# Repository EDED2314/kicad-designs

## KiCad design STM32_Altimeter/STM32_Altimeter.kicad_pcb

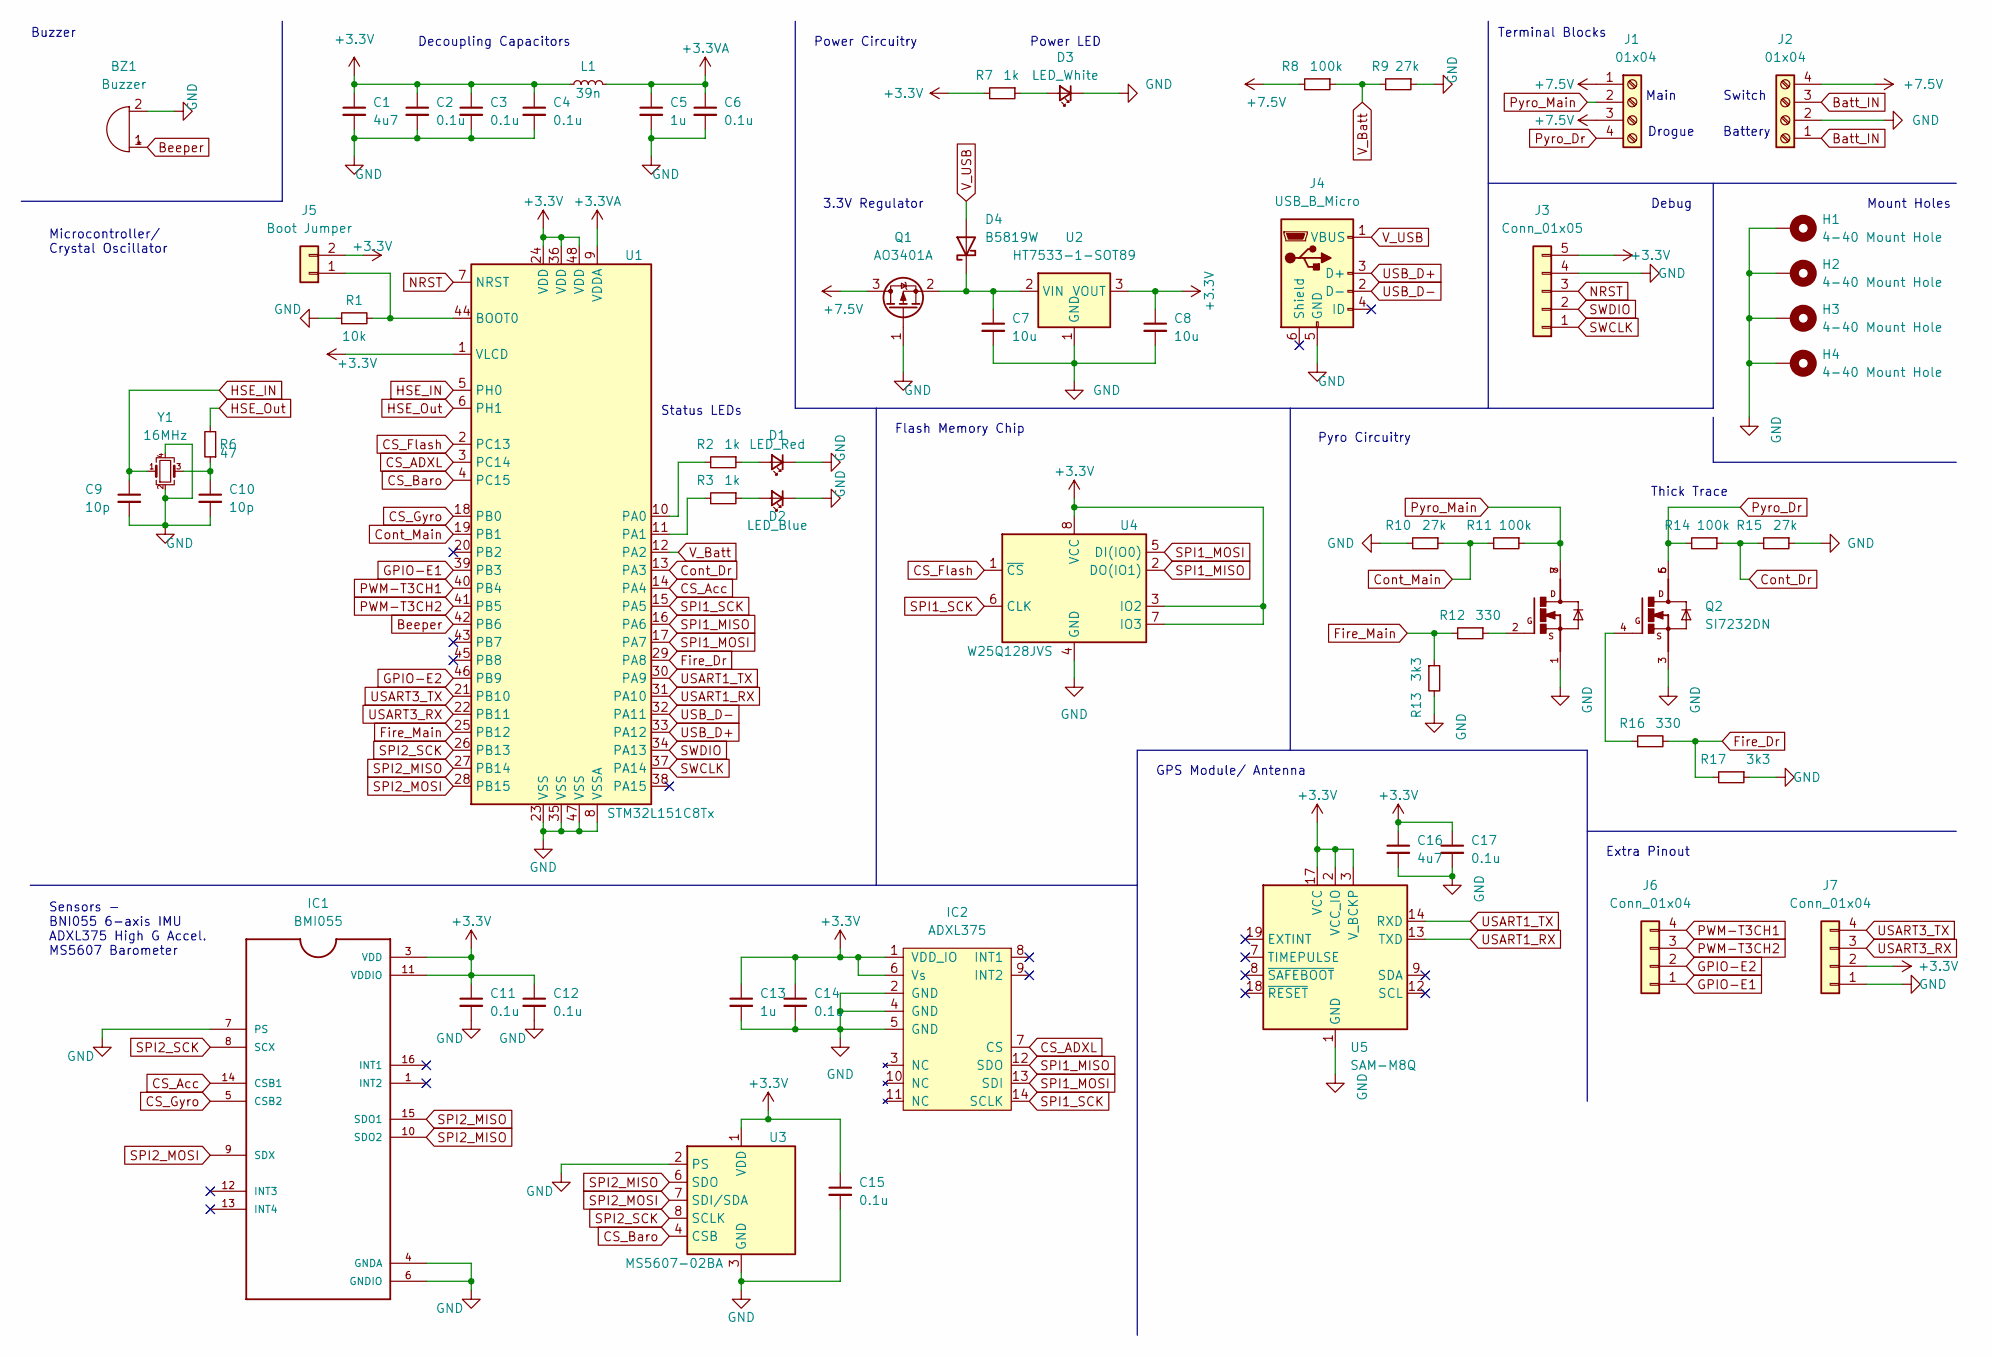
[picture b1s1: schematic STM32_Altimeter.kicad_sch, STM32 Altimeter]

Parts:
BZ1: Buzzer; Buzzer_12x9.5RM7.6
C1, C16: 4u7; C_0402_1005Metric
C2, C3, C4, C6, C11, C12, C14, C15, C17: 0.1u; C_0402_1005Metric
C5, C13: 1u; C_0402_1005Metric
C7, C8: 10u; C_1206_3216Metric
C9, C10: 10p; C_0402_1005Metric
D1: LED_Red; LED_0805_2012Metric
D2: LED_Blue; LED_0805_2012Metric
D3: LED_White; LED_0805_2012Metric
D4: B5819W; D_SOD-123
H1, H2, H3, H4: 4-40 Mount Hole; MountingHole_3.2mm_M3_DIN965_Pad
IC1: BMI055; QFN50P300X450X100-16N
IC2: ADXL375; LCC14P127_600X600X225L91X50N; Farnell 2361527
J1, J2: 01x04; TerminalBlock_MetzConnect_Type011_RT05504HBWC_1x04_P5.00mm_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
J3: Conn_01x05; PinHeader_1x05_P2.54mm_Vertical
J4: USB_B_Micro; USB_Micro-B_Molex-105017-0001
J5: Boot Jumper; PinHeader_1x02_P2.54mm_Vertical
J6: Conn_01x04; JST_SH_BM04B-SRSS-TB_04x1.00mm_Straight
J7: Conn_01x04
L1: 39n; L_0402_1005Metric
Q1: AO3401A; SOT-23
Q2: SI7232DN; TRANS_SI7232DN-T1-GE3
R1: 10k; R_0402_1005Metric
R2, R3, R7: 1k; R_0603_1608Metric
R6: 47; R_0402_1005Metric
R8, R11, R14: 100k; R_0603_1608Metric
R9, R10, R15: 27k; R_0603_1608Metric
R12, R16: 330; R_0402_1005Metric
R13, R17: 3k3; R_0402_1005Metric
U1: STM32L151C8Tx; LQFP-48_7x7mm_P0.5mm
U2: HT7533-1-SOT89; SOT-89-3
U3: MS5607-02BA; LGA-8_3x5mm_P1.25mm
U4: W25Q128JVS; SOIC-8_5.23x5.23mm_P1.27mm
U5: SAM-M8Q; ublox_SAM-M8Q
Y1: 16MHz; Crystal_SMD_3225-4Pin_3.2x2.5mm

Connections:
+3.3VA: C5.1, C6.1, L1.2, U1.9 (VDDA)
+7.5V: J1.1, J1.3, J2.4, Q1.3 (D), R8.2
Batt_IN: J2.1, J2.3
Beeper: BZ1.1 (-), U1.42 (PB6)
CS_ADXL: IC2.7 (CS), U1.3 (PC14)
CS_Acc: IC1.14 (CSB1), U1.14 (PA4)
CS_Baro: U1.4 (PC15), U3.4 (CSB), U3.5 (CSB)
CS_Gyro: IC1.5 (CSB2), U1.18 (PB0)
Cont_Main: R10.1, R11.2, U1.19 (PB1)
Fire_Dr: R16.2, R17.2, U1.29 (PA8)
Fire_Main: R12.2, R13.1, U1.25 (PB12)
GPIO-E1: J6.1, U1.39 (PB3)
GPIO-E2: J6.2, U1.46 (PB9)
HSE_IN: C9.1, U1.5 (PH0), Y1.1
HSE_Out: R6.2, U1.6 (PH1)
NRST: J3.3, U1.7 (NRST)
unnamed: C7.1, D4.1 (K), Q1.2 (S), U2.2 (VIN)
unnamed: C10.1, R6.1, Y1.3
unnamed: D1.2 (A), R2.1
unnamed: D2.2 (A), R3.1
unnamed: D3.2 (A), R7.1
unnamed: J5.1, R1.2, U1.44 (BOOT0)
unnamed: Q2.2, R12.1
unnamed: Q2.4, R16.1
unnamed: R2.2, U1.10 (PA0)
unnamed: R3.2, U1.11 (PA1)
PWM-T3CH1: J6.4, U1.40 (PB4)
PWM-T3CH2: J6.3, U1.41 (PB5)
Pyro_Dr: J1.4, Q2.5, Q2.6, R14.2
Pyro_Main: J1.2, Q2.7, Q2.8, R11.1
SPI1_MISO: IC2.12 (SDO), U1.16 (PA6), U4.2 (DO(IO1))
SPI1_MOSI: IC2.13 (SDI), U1.17 (PA7), U4.5 (DI(IO0))
SPI1_SCK: IC2.14 (SCLK), U1.15 (PA5), U4.6 (CLK)
SPI2_MOSI: IC1.9 (SDX), U1.28 (PB15), U3.7 (SDI/SDA)
SPI2_SCK: IC1.8 (SCX), U1.26 (PB13), U3.8 (SCLK)
SWCLK: J3.1, U1.37 (PA14)
SWDIO: J3.2, U1.34 (PA13)
USART1_RX: U1.31 (PA10), U5.13 (TXD)
USART1_TX: U1.30 (PA9), U5.14 (RXD)
USART3_RX: J7.3, U1.22 (PB11)
USART3_TX: J7.4, U1.21 (PB10)
USB_D+: J4.3 (D+), U1.33 (PA12)
USB_D-: J4.2 (D-), U1.32 (PA11)
V_Batt: R8.1, R9.2, U1.12 (PA2)
V_USB: D4.2 (A), J4.1 (VBUS)

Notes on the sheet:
Pyro Circuitry
Buzzer
Main
3.3V Regulator
Debug
Power Circuitry
Power LED
Terminal Blocks
GPS Module/ Antenna
Mount Holes
Switch
Microcontroller/ Crystal Oscillator
Status LEDs
Battery
Decoupling Capacitors
Sensors - BNI055 6-axis IMU ADXL375 High G Accel. MS5607 Barometer
Extra Pinout
Drogue
Thick Trace
Flash Memory Chip

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
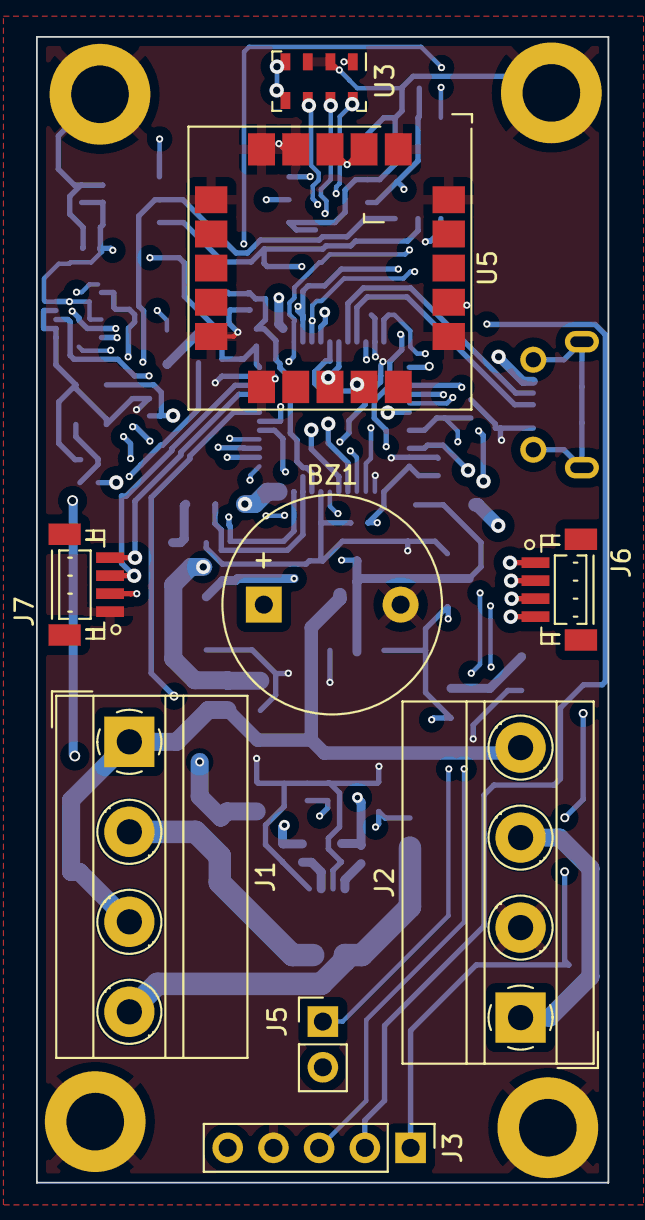
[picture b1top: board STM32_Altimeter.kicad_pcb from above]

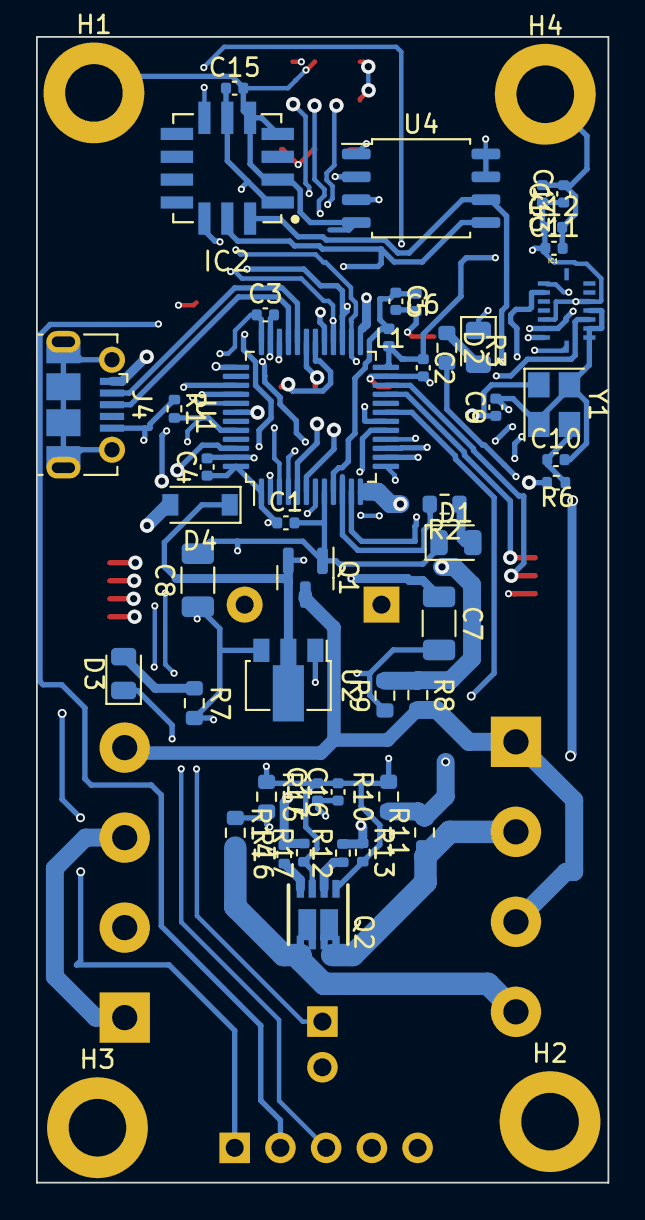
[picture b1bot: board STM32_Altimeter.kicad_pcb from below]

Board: 4 copper layers, 31.8 x 63.7 mm, 59 parts (50 on the bottom side), 48 nets.

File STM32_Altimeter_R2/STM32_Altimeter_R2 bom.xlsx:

Comment | Designator | Footprint | JLCPCB Part #
Buzzer Buzzer, polarized | BZ1 | Buzzer_12x9.5RM7.6 | C64777
4u7 Unpolarized capacitor, small symbol | C1,C16 | C_0402_1005Metric | C19666
0.1u Unpolarized capacitor, small symbol | C2,C3,C4,C6,C11,C12,C14,C15,C17 | C_0402_1005Metric | C13585
1u Unpolarized capacitor, small symbol | C5,C13 | C_0402_1005Metric | C32949
10u Unpolarized capacitor, small symbol | C7,C8 | C_1206_3216Metric | C52923
10p Unpolarized capacitor, small symbol | C9,C10 | C_0402_1005Metric | C307331
LED_Red Light emitting diode, small symbol | D1 | LED_0805_2012Metric | C2286
LED_Blue Light emitting diode, small symbol | D2 | LED_0805_2012Metric | C72041
LED_White Light emitting diode, small symbol | D3 | LED_0805_2012Metric | C2290
B5819W Schottky diode | D4 | D_SOD-123 | C8598
4-40 Mount Hole Mounting Hole with connection | H1,H2,H3,H4 | MountingHole_3.2mm_M3_DIN965_Pad
BMI055 | IC1 | QFN50P300X450X100-16N | C189620
ADXL375 | IC2 | PQFN80P300X500X100-14N | C481898
01x04 Generic screw terminal, single row, 01x04, script generated (kicad-librar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 | J1,J2 | TerminalBlock_MetzConnect_Type011_RT05504HBWC_1x04_P5.00mm_Horizontal
Conn_01x05 Generic connector, single row, 01x05, script generated (kicad-librar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 | J3 | PinHeader_1x05_P2.54mm_Vertical
USB_B_Micro USB Micro Type B connector | J4 | USB_Micro-B_Molex-105017-0001 | C136000
Boot Jumper Generic connector, single row, 01x02, script generated (kicad-libra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 | J5 | PinHeader_1x02_P2.54mm_Vertical
Conn_01x04 Generic connector, single row, 01x04, script generated (kicad-librar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 | J6 | JST_SH_BM04B-SRSS-TB_04x1.00mm_Straight
39n Inductor, small symbol | L1 | L_0402_1005Metric | C26443
AO3401A -4.0A Id, -30V Vds, P-Channel MOSFET, SOT-23 | Q1 | SOT-23 | C15127
SI5997DU-T1-GE3 | Q2 | TRANS_SI5997DU-T1-GE3 | C141554
10k Resistor, small symbol | R1 | R_0402_1005Metric | C25744
1k Resistor, small symbol | R2,R3,R7 | R_0603_1608Metric | C21190
200 Resistor, small symbol | R4 | R_0402_1005Metric | C25744
47 Resistor, small symbol | R6 | R_0402_1005Metric | C25118
100k Resistor, small symbol | R8,R11,R14 | R_0603_1608Metric | C25803
27k Resistor, small symbol | R9,R10,R15 | R_0603_1608Metric | C22967
330 Resistor, small symbol | R12,R16 | R_0402_1005Metric | C25890
3k3 Resistor, small symbol | R13,R17 | R_0402_1005Metric | C137993
STM32L151C8Tx ARM Cortex-M3 MCU, 64KB flash, 10KB RAM, 32MHz, 1.65-3.6V, 37 GPI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 | U1 | LQFP-48_7x7mm_P0.5mm | C9861
HT7533-1-SOT89 100mA Low Dropout Voltage Regulator, Fixed Output, SOT89 | U2 | SOT-89-3 | C14289
MS5607-02BA Barometric pressure sensor, 20cm resolution, 10 to 1200 mbar, I2C a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 | U3 | LGA-8_3x5mm_P1.25mm
W25Q128JVS 128Mb Serial Flash Memory, Standard/Dual/Quad SPI, SOIC-8 | U4 | SOIC-8_5.23x5.23mm_P1.27mm | C97521
SAM-M8Q GPS ublox M8 variant | U5 | ublox_SAM-M8Q | C97521
16MHz Four pin crystal, GND on pins 2 and 4, small symbol | Y1 | Crystal_SMD_3225-4Pin_3.2x2.5mm | C13738

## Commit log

2022-08-17 init
